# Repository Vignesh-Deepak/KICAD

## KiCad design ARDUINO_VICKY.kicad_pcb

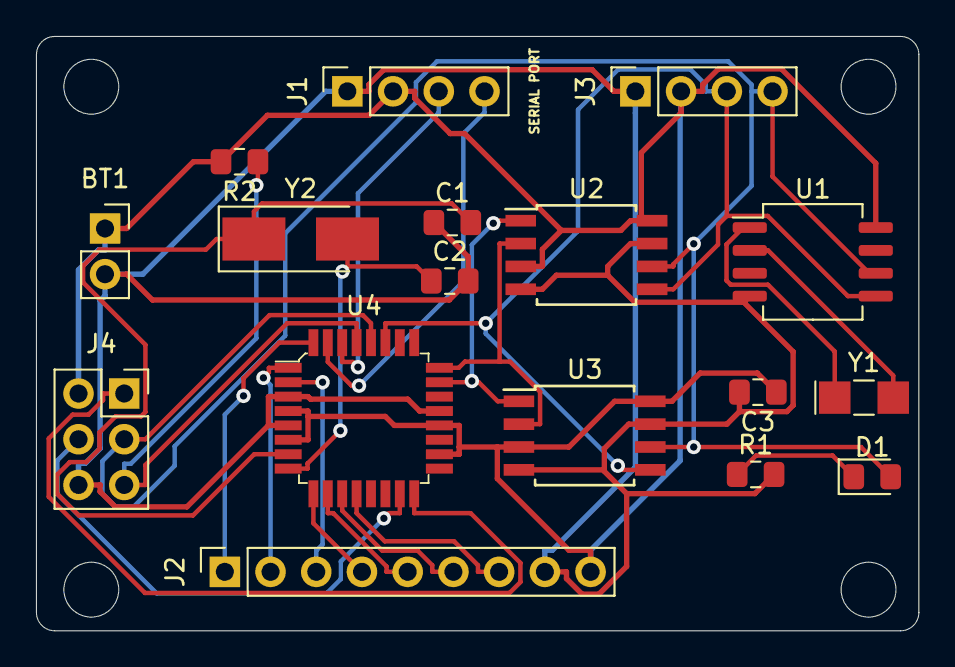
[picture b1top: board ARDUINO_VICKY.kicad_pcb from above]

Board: 2 copper layers, 49.0 x 33.0 mm, 17 parts (0 on the bottom side), 23 nets.

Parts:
BT1: Battery 3V; PinSocket_1x02_P2.54mm_Vertical
C1, C2: 22PICO FARAD; C_0805_2012Metric_Pad1.15x1.40mm_HandSolder
C3: 10MICRO FARAD; C_0805_2012Metric_Pad1.15x1.40mm_HandSolder
D1: LED; LED_0805_2012Metric_Pad1.15x1.40mm_HandSolder
J1: SERIAL PORT; PinSocket_1x04_P2.54mm_Vertical
J2: DIGITAL PINS; PinSocket_1x09_P2.54mm_Vertical
J3: I2C; PinSocket_1x04_P2.54mm_Vertical
J4: ICSP; PinSocket_2x03_P2.54mm_Vertical
R1: 330 OHMS; R_0805_2012Metric_Pad1.15x1.40mm_HandSolder
R2: 10K OHMS; R_0805_2012Metric_Pad1.15x1.40mm_HandSolder
U1: DS1337S+; SO-8_5.3x6.2mm_P1.27mm
U2, U3: 24LC1025; SOIJ-8_5.3x5.3mm_P1.27mm
U4: ATMEGA328P-AU; TQFP-32_7x7mm
Y1: 32 MHZ; Crystal_SMD_MicroCrystal_CC7V-T1A-2Pin_3.2x1.5mm_HandSolder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
Y2: 16MHZ; Crystal_SMD_5032-2Pin_5.0x3.2mm_HandSoldering

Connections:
/ADDS1: U2.1, U3.1, U4.23
/ADDS2: U2.2, U3.2, U4.24
/D2: J2.1, U4.32
/D3: J2.2, U4.1
/D4: J2.3, U4.2
/D5: J2.4, U4.9
/D6: J2.5, U4.10
/D7: J2.6, U4.11
/D8: J2.7, U4.12
/MISO: J4.1, U4.16
/MOSI: J4.4, U4.15
/RESET: J4.5, R2.1, U4.29
/RX: J1.3, U4.30
/SCL: D1.2, J3.4, J4.3, U1.6, U2.6, U3.6, U4.28
/SDA: J3.3, U1.5, U2.5, U3.5, U4.27
/TX: J1.4, U4.31
/VCC: BT1.1, C3.1, J1.2, J2.9, J3.2, J4.2, R2.2, U1.8, U2.3, U2.8, U3.3, U3.8, U4.4, U4.6, U4.18, U4.20
GNDPWR: BT1.2, C1.1, C2.2, C3.2, J1.1, J2.8, J3.1, J4.6, R1.2, U1.4, U2.4, U2.7, U3.4, U3.7, U4.3, U4.5, U4.21
unnamed: C1.2, U4.7, Y2.1
unnamed: C2.1, U4.8, Y2.2
unnamed: D1.1, R1.1
unnamed: U1.1, Y1.1
unnamed: U1.2, Y1.2

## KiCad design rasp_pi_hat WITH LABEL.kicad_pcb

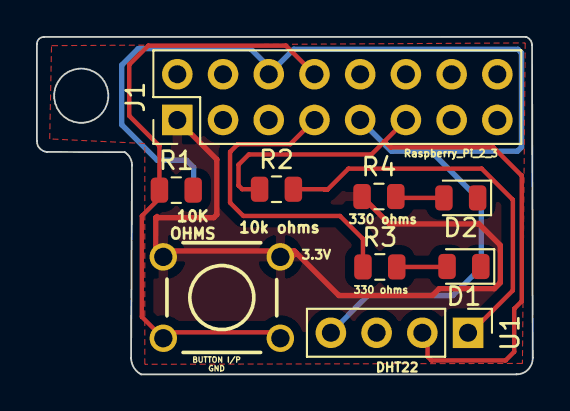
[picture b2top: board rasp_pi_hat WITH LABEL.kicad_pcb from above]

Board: 2 copper layers, 27.5 x 18.7 mm, 9 parts (0 on the bottom side), 8 nets.

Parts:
D1, D2: LED; LED_0805_2012Metric
J1: Raspberry_Pi_2_3; PinHeader_2x08_P2.54mm_Vertical
R1, R2: 10k ohms; R_0805_2012Metric
R3, R4: 330 ohms; R_0805_2012Metric
SW1: SW_DPST; SW_PUSHBUTTON_PTH
U1: DHT11; PinHeader_1x04_P2.54mm_Vertical

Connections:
/3V3: J1.1, R4.1, SW1.1
/button_input: J1.8, R1.1, SW1.2
GND: D1.1, D2.1, J1.6, J1.9, R1.2, U1.4
unnamed: D1.2, R3.2
unnamed: D2.2, R4.2
unnamed: J1.7, R3.1
unnamed: J1.11, R2.1, U1.2
unnamed: R2.2, U1.1

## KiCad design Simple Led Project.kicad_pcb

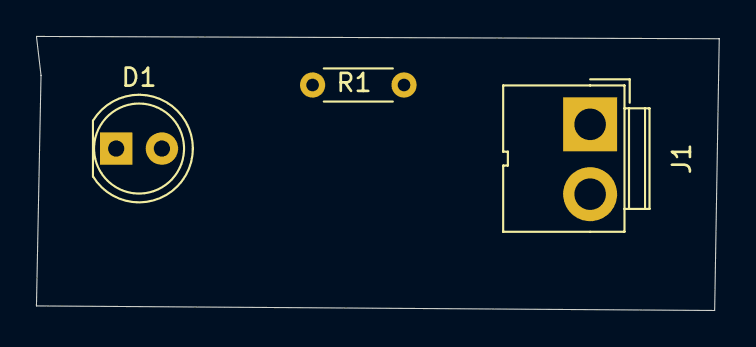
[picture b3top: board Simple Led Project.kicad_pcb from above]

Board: 2 copper layers, 37.9 x 15.2 mm, 3 parts (0 on the bottom side), 3 nets, no tracks yet.

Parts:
D1: LED; LED_D5.0mm
J1: CONN_02PTH2; JWT_A3963_1x02_P3.96mm_Vertical
R1: RESISTOR0402; R_Axial_DIN0204_L3.6mm_D1.6mm_P5.08mm_Horizontal

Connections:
+5V: J1.1, R1.2
GND: D1.1, J1.2
unnamed: D1.2, R1.1

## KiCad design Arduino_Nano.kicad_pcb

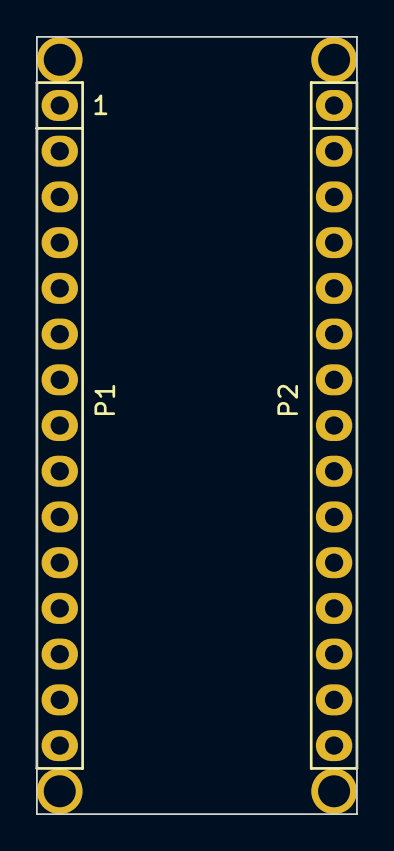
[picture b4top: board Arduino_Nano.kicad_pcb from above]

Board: 2 copper layers, 17.8 x 43.2 mm, 6 parts (0 on the bottom side), 2 nets, no tracks yet.

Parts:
P1: Digital; Socket_Strip_Arduino_1x15
P2: Analog; Socket_Strip_Arduino_1x15
P3, P4, P5, P6: CONN_01X01; 1pin_Nano

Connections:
/Reset: P1.3, P2.3
GND: P1.4, P2.2

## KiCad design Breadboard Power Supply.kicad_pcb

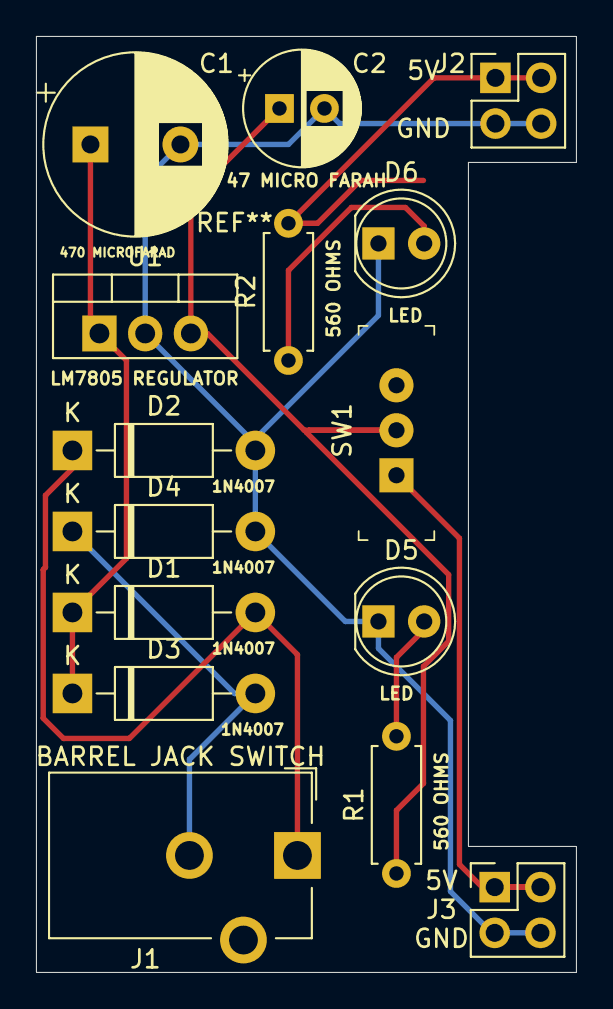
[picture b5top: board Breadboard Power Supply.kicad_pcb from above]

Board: 2 copper layers, 30.0 x 52.0 mm, 15 parts (0 on the bottom side), 8 nets.

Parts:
C1: 470 micro farad; CP_Radial_D10.0mm_P5.00mm
C2: 47 micro farad; CP_Radial_D6.3mm_P2.50mm
D1, D2, D3, D4: 1N4007; D_DO-41_SOD81_P10.16mm_Horizontal
D5, D6: LED; LED_D5.0mm
J1: Barrel_Jack_Switch; BarrelJack_CUI_PJ-102AH_Horizontal
J2, J3: Conn_02x02_Odd_Even; PinHeader_2x02_P2.54mm_Vertical
R1, R2: 560 ohms; R_Axial_DIN0207_L6.3mm_D2.5mm_P7.62mm_Horizontal
SW1: SW_DPDT_x2; Switch_Slide_11.6x4mm_EG1218
U1: LM7805_TO220; TO-220-3_Vertical

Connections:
/VOUT2: J2.1, J2.2, J3.1, J3.2, R2.2, SW1.1
/Vin: C1.1, D1.1, D3.1, U1.1
/Vout: C1.2, C2.2, D2.2, D4.2, D5.1, D6.1, J2.3, J2.4, J3.3, J3.4, U1.2
/Vout1: C2.1, R1.1, SW1.2, U1.3
unnamed: D1.2, D2.1, J1.1
unnamed: D3.2, D4.1, J1.2
unnamed: D5.2, R1.2
unnamed: D6.2, R2.1
